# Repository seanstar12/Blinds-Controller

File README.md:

# Blinds-Controller
 PCB for automated blinds running Tasmota

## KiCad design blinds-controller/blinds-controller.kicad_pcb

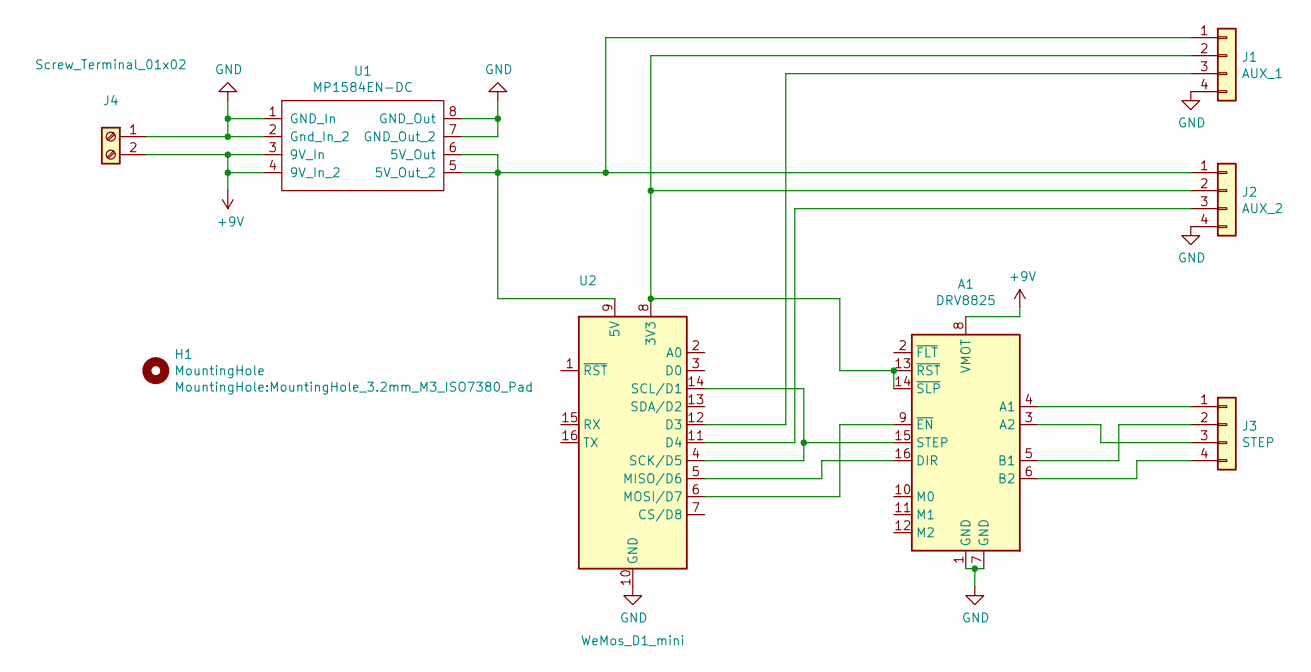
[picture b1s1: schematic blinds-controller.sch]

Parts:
A1: DRV8825
H1: MountingHole; MountingHole_3.2mm_M3_ISO7380_Pad
J1: AUX_1; PinHeader_1x04_P2.54mm_Vertical
J2: AUX_2; PinHeader_1x04_P2.54mm_Vertical
J3: STEP; PinHeader_1x04_P2.54mm_Vertical
J4: Screw_Terminal_01x02; Altech_AK300_1x02_P5.00mm_45-Degree
U1: MP1584EN-DC
U2: WeMos_D1_mini; WEMOS_D1_mini_light

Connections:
+9V: A1.8 (VMOT), J4.2, U1.3 (9V_In), U1.4 (9V_In_2)
GND: A1.1 (GND), A1.7 (GND), J1.4, J2.4, J4.1, U1.1 (GND_In), U1.2 (Gnd_In_2), U1.7 (GND_Out_2), U1.8 (GND_Out), U2.10 (GND)
unnamed: A1.3 (A2), J3.3
unnamed: A1.4 (A1), J3.1
unnamed: A1.5 (B1), J3.2
unnamed: A1.6 (B2), J3.4
unnamed: A1.9 (~EN), U2.6 (MOSI/D7)
unnamed: A1.13 (~RST), A1.14 (~SLP), J1.2, J2.2, U2.8 (3V3)
unnamed: A1.15 (STEP), U2.4 (SCK/D5), U2.14 (SCL/D1)
unnamed: A1.16 (DIR), U2.5 (MISO/D6)
unnamed: J1.1, J2.1, U1.5 (5V_Out_2), U1.6 (5V_Out), U2.9 (5V)
unnamed: J1.3, U2.12 (D3)
unnamed: J2.3, U2.11 (D4)

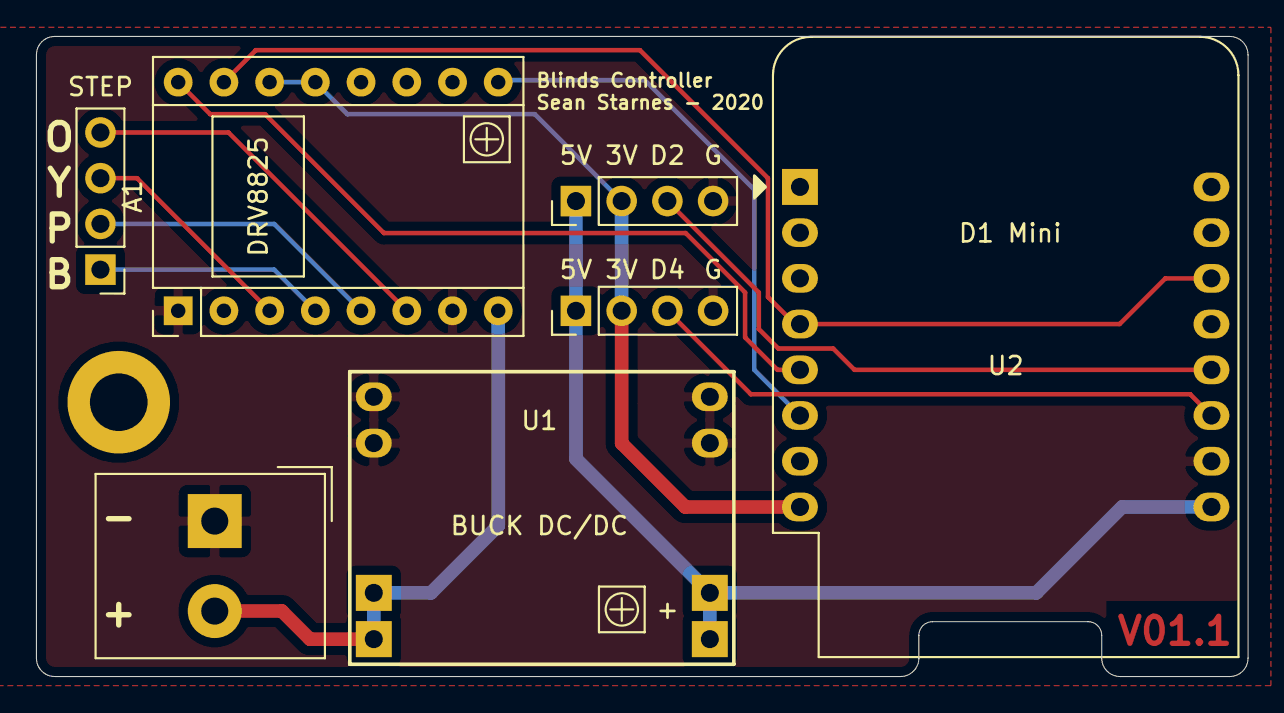
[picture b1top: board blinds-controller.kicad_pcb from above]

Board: 2 copper layers, 67.3 x 35.6 mm, 8 parts (0 on the bottom side), 13 nets.

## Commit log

2020-11-05 Rev 2 of PCB

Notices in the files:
blinds-controller/blinds-controller.kicad_pcb:
License: CC BY 4.0
